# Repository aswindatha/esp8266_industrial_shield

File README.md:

# esp8266_industrial_shield

Industrial 8-channel motor controller (ESP32-WROOM-32E), 100 × 100 mm.

## Repository structure

| Path | What it is |
|---|---|
| **`2layer_production/`** | **FINAL, fabrication-ready board.** 0 DRC, 0 ERC, complete fab package and quotation. Use this. |
| **`1layer_prototype/`** | Single-layer conversion experiment. **Not fabrication-ready** (18 unconnected). Study only. |
| `tools/` | Routing, auditing and BOM scripts used to verify the boards. |
| `robu-search/` | Portable Robu.in part-search skill kit (installed into OpenCode). |

The root-level `ind_8ch_motor_ctrl.*` files are the working copy of the
2-layer production board (identical to `2layer_production/`).

## 2-layer production board — status

- **PCB DRC:** 0 violations, 0 unconnected (all severities)
- **ERC:** 0 violations
- **Production audit:** 23/23 checks PASS (`python3 tools/production_audit.py`)
- **Layers:** 2 Cu, 716 track segments, 83 vias, 50 components all on F.Cu
- **Min features:** 0.2624 mm track, 0.2516 mm clearance, 0.20 mm drill, 0.30 mm copper-to-edge
- **Fab package:** `2layer_production/ind_8ch_motor_ctrl_FAB_PACKAGE.zip` (24 files)

See `2layer_production/README.md` and `FINAL_VERIFICATION.md` for full evidence.

## Prototype quotation (5 boards, 2026-11-23)

| Item | ₹ |
|---|---:|
| PCB (cuCircuits, FR4 TG135, 1.6 mm, HASL-RoHs, tested) | 1,692.75 |
| Components (Robu.in, verified) | 3,860.55 |
| **Subtotal (excl. terminal blocks & shipping)** | **5,553.30** |

Source: `COST_REPORT.md`.

## Important limitations

- **Single-layer:** not achievable as a DRC-clean board with the current netlist
  and KiCad's copper-only connectivity model. Full analysis in
  `SINGLE_LAYER_FINAL.md` and `1layer_prototype/README.md`.
- **India compliance:** WPC ETA required for the ESP32 2.4 GHz radio; RoHS CoCs
  needed. See `INDIA_MANUFACTURING_REPORT.md`.
- **Firmware:** ESP32 IO0/EN are not broken out — pre-flash firmware.
- **Next revision:** add an input fuse, flyback diodes and extra decoupling
  capacitors via a proper re-layout (they could not be inserted into the
  finished copper without breaking DRC).

## Reproduce verification

```bash
kicad-cli pcb drc --exit-code-violations 2layer_production/ind_8ch_motor_ctrl.kicad_pcb
kicad-cli sch erc --exit-code-violations 2layer_production/ind_8ch_motor_ctrl.kicad_sch
python3 tools/production_audit.py
```

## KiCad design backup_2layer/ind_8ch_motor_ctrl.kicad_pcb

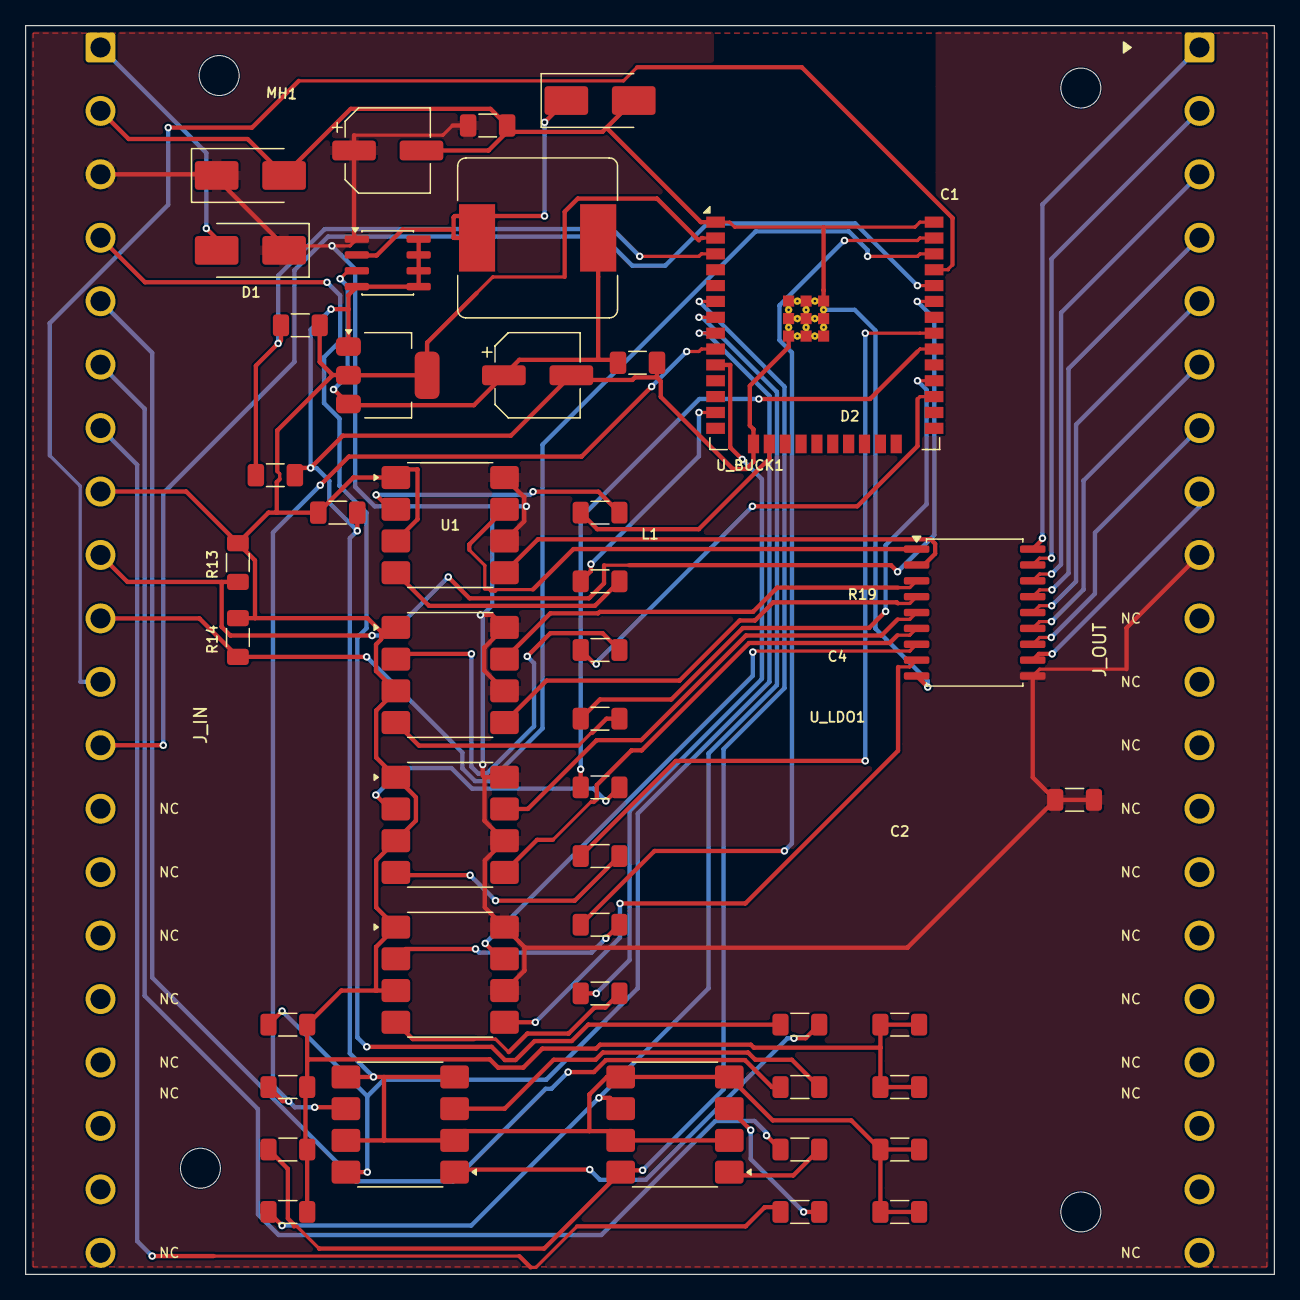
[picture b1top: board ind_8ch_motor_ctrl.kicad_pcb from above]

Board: 2 copper layers, 100.0 x 100.0 mm, 50 parts (0 on the bottom side), 55 nets.

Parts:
C1, C2, C3, C4: 10uF; C_1206_3216Metric_Pad1.33x1.80mm_HandSolder
C_BULK1, C_BULK2: 220uF/25V; CP_Elec_6.3x7.7
D1, D2: SS34; D_SMB_Handsoldering
D_TVS1: SMBJ15A-13-F; D_SMB_Handsoldering
J_IN: INPUT; TerminalBlock_CUI_TB007-508-20_1x20_P5.08mm_Horizontal
J_OUT: OUTPUT; TerminalBlock_CUI_TB007-508-20_1x20_P5.08mm_Horizontal
L1: 33uH; L_Bourns_SRR1260
MH1, MH2, MH3, MH4: MountingHole_3.2mm
R1, R2, R3, R4, R5, R6, R7, R8: 330R; R_1206_3216Metric_Pad1.30x1.75mm_HandSolder
R9, R10, R11, R12: 2.2k; R_1206_3216Metric_Pad1.30x1.75mm_HandSolder
R13, R14, R15, R16, R17, R18: 4.7k; R_1206_3216Metric_Pad1.30x1.75mm_HandSolder
R19: 10k; R_1206_3216Metric_Pad1.30x1.75mm_HandSolder
R_J1, R_J2, R_J3, R_J4, R_J5: 0R; R_1206_3216Metric_Pad1.30x1.75mm_HandSolder
U1, U2, U3, U4, U5, U6: LTV-827S; SOP-8_6.605x9.655mm_P2.54mm
U_BUCK1: XL1509-5.0; SOIC-8_3.9x4.9mm_P1.27mm
U_DRV1: ULN2803; SOIC-18W_7.5x11.6mm_P1.27mm
U_LDO1: AMS1117-3.3; SOT-223-3_TabPin2
U_MCU1: ESP32-WROOM-32E

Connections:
/3V3_RAIL: C3.1, J_IN.8, R13.2, R14.2, R15.2, R16.2, R17.2, R18.2, R19.2, R_J1.1, R_J1.2, R_J2.1, R_J2.2, U1.1, U1.3, U2.1, U2.3, U3.1, U3.3, U4.1, U4.3, U_LDO1.2 (VO), U_MCU1.2 (VDD)
/5V_RAIL: C2.1, C_BULK2.1, L1.2, U_BUCK1.3 (FB), U_LDO1.3 (VI)
/12V_PROT: C1.1, C_BULK1.1, D1.1 (K), D_TVS1.1 (K), J_IN.3, J_OUT.9, R_J4.1, R_J4.2, U1.6, U1.8, U2.6, U2.8, U3.6, U3.8, U4.6, U4.8, U_BUCK1.1 (VIN), U_DRV1.10 (COM)
/12V_RAW: D1.2 (A), J_IN.1
/GND: C1.2, C2.2, C3.2, C4.2, C_BULK1.2, C_BULK2.2, D2.2 (A), D_TVS1.2 (A), J_IN.2, R_J3.1, R_J3.2, R_J5.1, R_J5.2, U5.2, U5.4, U5.5, U5.7, U6.2, U6.4, U6.5, U6.7, U_BUCK1.4 (~EN), U_BUCK1.5 (GND), U_BUCK1.6 (GND), U_BUCK1.7 (GND), U_BUCK1.8 (GND), U_DRV1.9 (GND), U_LDO1.1 (GND), U_MCU1.1 (GND), U_MCU1.15 (GND), U_MCU1.38 (GND), U_MCU1.39 (GND)
/I2C_SCL: J_IN.10, R14.1, U_MCU1.36 (IO22)
/I2C_SDA: J_IN.9, R13.1, U_MCU1.33 (IO21)
/M1_DRV: U1.7, U_DRV1.1 (I1)
/M1_GPIO: R2.1, U_MCU1.13 (IO14)
/M1_LED: R1.2, U1.2
/M2_DRV: U1.5, U_DRV1.2 (I2)
/M2_GPIO: R3.1, U_MCU1.27 (IO16)
/M2_LED: R2.2, U1.4
/M3_DRV: U2.7, U_DRV1.3 (I3)
/M3_GPIO: R4.1, U_MCU1.28 (IO17)
/M3_LED: R3.2, U2.2
/M4_DRV: U2.5, U_DRV1.4 (I4)
/M4_GPIO: R1.1, U_MCU1.16 (IO13)
/M4_LED: R4.2, U2.4
/M5_DRV: U3.7, U_DRV1.5 (I5)
/M5_GPIO: R8.1, U_MCU1.10 (IO25)
/M5_LED: R5.2, U3.2
/M6_DRV: U3.5, U_DRV1.6 (I6)
/M6_GPIO: R5.1, U_MCU1.30 (IO18)
/M6_LED: R6.2, U3.4
/M7_DRV: U4.7, U_DRV1.7 (I7)
/M7_GPIO: R6.1, U_MCU1.31 (IO19)
/M7_LED: R7.2, U4.2
/M8_DRV: U4.5, U_DRV1.8 (I8)
/M8_GPIO: R7.1, U_MCU1.37 (IO23)
/M8_LED: R8.2, U4.4
/MCU_EN: C4.1, R19.1, U_MCU1.3 (EN)
/MOT1: J_OUT.1, U_DRV1.18 (O1)
/MOT2: J_OUT.2, U_DRV1.17 (O2)
/MOT3: J_OUT.3, U_DRV1.16 (O3)
/MOT4: J_OUT.4, U_DRV1.15 (O4)
/MOT5: J_OUT.5, U_DRV1.14 (O5)
/MOT6: J_OUT.6, U_DRV1.13 (O6)
/MOT7: J_OUT.7, U_DRV1.12 (O7)
/MOT8: J_OUT.8, U_DRV1.11 (O8)
/SENS1_A: R9.2, U5.1
/SENS1_COL: R15.1, U5.8, U_MCU1.8 (IO32)
/SENS2_A: R10.2, U5.3
/SENS2_COL: R16.1, U5.6, U_MCU1.9 (IO33)
/SENS3_A: R11.2, U6.1
/SENS3_COL: R17.1, U6.8, U_MCU1.6 (IO34)
/SENS4_A: R12.2, U6.3
/SENS4_COL: R18.1, U6.6, U_MCU1.7 (IO35)
/SENS_IN1: J_IN.4, R9.1
/SENS_IN2: J_IN.5, R10.1
/SENS_IN3: J_IN.6, R11.1
/SENS_IN4: J_IN.7, R12.1
/SW_BUCK: D2.1 (K), L1.1, U_BUCK1.2 (OUT)
/UART_RX: J_IN.12, U_MCU1.34 (RXD0/IO3)
/UART_TX: J_IN.11, U_MCU1.35 (TXD0/IO1)

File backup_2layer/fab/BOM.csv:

Reference,Value,Footprint,Pads,Side
R_J1,0R,Resistor_SMD:R_1206_3216Metric_Pad1.30x1.75mm_HandSolder,2,F.Cu
R_J2,0R,Resistor_SMD:R_1206_3216Metric_Pad1.30x1.75mm_HandSolder,2,F.Cu
R_J3,0R,Resistor_SMD:R_1206_3216Metric_Pad1.30x1.75mm_HandSolder,2,F.Cu
R_J4,0R,Resistor_SMD:R_1206_3216Metric_Pad1.30x1.75mm_HandSolder,2,F.Cu
R_J5,0R,Resistor_SMD:R_1206_3216Metric_Pad1.30x1.75mm_HandSolder,2,F.Cu
R19,10k,Resistor_SMD:R_1206_3216Metric_Pad1.30x1.75mm_HandSolder,2,F.Cu
C1,10uF,Capacitor_SMD:C_1206_3216Metric_Pad1.33x1.80mm_HandSolder,2,F.Cu
C2,10uF,Capacitor_SMD:C_1206_3216Metric_Pad1.33x1.80mm_HandSolder,2,F.Cu
C3,10uF,Capacitor_SMD:C_1206_3216Metric_Pad1.33x1.80mm_HandSolder,2,F.Cu
C4,10uF,Capacitor_SMD:C_1206_3216Metric_Pad1.33x1.80mm_HandSolder,2,F.Cu
R10,2.2k,Resistor_SMD:R_1206_3216Metric_Pad1.30x1.75mm_HandSolder,2,F.Cu
R11,2.2k,Resistor_SMD:R_1206_3216Metric_Pad1.30x1.75mm_HandSolder,2,F.Cu
R12,2.2k,Resistor_SMD:R_1206_3216Metric_Pad1.30x1.75mm_HandSolder,2,F.Cu
R9,2.2k,Resistor_SMD:R_1206_3216Metric_Pad1.30x1.75mm_HandSolder,2,F.Cu
C_BULK1,220uF/25V,Capacitor_SMD:CP_Elec_6.3x7.7,2,F.Cu
C_BULK2,220uF/25V,Capacitor_SMD:CP_Elec_6.3x7.7,2,F.Cu
R1,330R,Resistor_SMD:R_1206_3216Metric_Pad1.30x1.75mm_HandSolder,2,F.Cu
R2,330R,Resistor_SMD:R_1206_3216Metric_Pad1.30x1.75mm_HandSolder,2,F.Cu
R3,330R,Resistor_SMD:R_1206_3216Metric_Pad1.30x1.75mm_HandSolder,2,F.Cu
R4,330R,Resistor_SMD:R_1206_3216Metric_Pad1.30x1.75mm_HandSolder,2,F.Cu
R5,330R,Resistor_SMD:R_1206_3216Metric_Pad1.30x1.75mm_HandSolder,2,F.Cu
R6,330R,Resistor_SMD:R_1206_3216Metric_Pad1.30x1.75mm_HandSolder,2,F.Cu
R7,330R,Resistor_SMD:R_1206_3216Metric_Pad1.30x1.75mm_HandSolder,2,F.Cu
R8,330R,Resistor_SMD:R_1206_3216Metric_Pad1.30x1.75mm_HandSolder,2,F.Cu
L1,33uH,Inductor_SMD:L_Bourns_SRR1260,2,F.Cu
R13,4.7k,Resistor_SMD:R_1206_3216Metric_Pad1.30x1.75mm_HandSolder,2,F.Cu
R14,4.7k,Resistor_SMD:R_1206_3216Metric_Pad1.30x1.75mm_HandSolder,2,F.Cu
R15,4.7k,Resistor_SMD:R_1206_3216Metric_Pad1.30x1.75mm_HandSolder,2,F.Cu
R16,4.7k,Resistor_SMD:R_1206_3216Metric_Pad1.30x1.75mm_HandSolder,2,F.Cu
R17,4.7k,Resistor_SMD:R_1206_3216Metric_Pad1.30x1.75mm_HandSolder,2,F.Cu
R18,4.7k,Resistor_SMD:R_1206_3216Metric_Pad1.30x1.75mm_HandSolder,2,F.Cu
U_LDO1,AMS1117-3.3,Package_TO_SOT_SMD:SOT-223-3_TabPin2,4,F.Cu
U_MCU1,ESP32-WROOM-32E,RF_Module:ESP32-WROOM-32E,59,F.Cu
J_IN,INPUT,TerminalBlock_CUI_TB007-508-20_1x20_P5.08mm_Horizontal,20,F.Cu
U1,LTV-827S,Package_SO:SOP-8_6.605x9.655mm_P2.54mm,8,F.Cu
U2,LTV-827S,Package_SO:SOP-8_6.605x9.655mm_P2.54mm,8,F.Cu
U3,LTV-827S,Package_SO:SOP-8_6.605x9.655mm_P2.54mm,8,F.Cu
U4,LTV-827S,Package_SO:SOP-8_6.605x9.655mm_P2.54mm,8,F.Cu
U5,LTV-827S,Package_SO:SOP-8_6.605x9.655mm_P2.54mm,8,F.Cu
U6,LTV-827S,Package_SO:SOP-8_6.605x9.655mm_P2.54mm,8,F.Cu
J_OUT,OUTPUT,TerminalBlock_CUI_TB007-508-20_1x20_P5.08mm_Horizontal,20,F.Cu
D_TVS1,SMBJ15A-13-F,Diode_SMD:D_SMB_Handsoldering,2,F.Cu
D1,SS34,Diode_SMD:D_SMB_Handsoldering,2,F.Cu
D2,SS34,Diode_SMD:D_SMB_Handsoldering,2,F.Cu
U_DRV1,ULN2803,Package_SO:SOIC-18W_7.5x11.6mm_P1.27mm,18,F.Cu
U_BUCK1,XL1509-5.0,Package_SO:SOIC-8_3.9x4.9mm_P1.27mm,8,F.Cu

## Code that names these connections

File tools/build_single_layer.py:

"""
Build the SINGLE-LAYER variant (working copy). The 2-layer design is preserved in
ind_8ch_motor_ctrl_2LAYER_backup.zip and backup_2layer/.

Changes vs 2-layer version:
  - B.Cu copper removed entirely (no tracks, no vias, no zones)
  - 5.08 mm CUI terminal blocks replaced with 5.00 mm Altech AK100 20-position
    blocks (101.05 mm body instead of 103.25 mm -> ~0.5 mm overhang per end)
  - terminal blocks repositioned to y=2.5 for symmetric end overhang
"""
import pcbnew, os
ROOT=os.path.dirname(os.path.dirname(os.path.abspath(__file__)))
PCB=os.path.join(ROOT,"ind_8ch_motor_ctrl.kicad_pcb")
LIB=r"C:\Users\aswin\AppData\Local\Programs\KiCad\10.0\share\kicad\footprints"
TBLIB="TerminalBlock_Altech.pretty"
TBNAME="Altech_AK100_1x20_P5.00mm"
MM=pcbnew.FromMM
V=lambda x,y: pcbnew.VECTOR2I(MM(x),MM(y))

IN_PINS={1:"12V_RAW",2:"GND",3:"12V_PROT",4:"SENS_IN1",5:"SENS_IN2",6:"SENS_IN3",7:"SENS_IN4",
         8:"3V3_RAIL",9:"I2C_SDA",10:"I2C_SCL",11:"UART_TX",12:"UART_RX"}
OUT_PINS={1:"MOT1",2:"MOT2",3:"MOT3",4:"MOT4",5:"MOT5",6:"MOT6",7:"MOT7",8:"MOT8",9:"12V_PROT"}
USED=set(IN_PINS.values())|set(OUT_PINS.values())
TB_POS={"J_IN":(6.0,2.5),"J_OUT":(94.0,2.5)}

b=pcbnew.LoadBoard(PCB)
print("loaded footprints:",len(list(b.GetFootprints())))

# 1) wipe all routing and zones (both layers)
for t in list(b.GetTracks()): b.RemoveNative(t)
for z in list(b.Zones()): b.RemoveNative(z)
print("cleared tracks/zones")

# 2) remove old TBs and add 5.00 mm ones
for ref in ("J_IN","J_OUT"):
    fp=b.FindFootprintByReference(ref)
    if fp: b.RemoveNative(fp)
nets={n:b.FindNet("/"+n) for n in USED}
for ref,pinmap in (("J_IN",IN_PINS),("J_OUT",OUT_PINS)):
    fp=pcbnew.FootprintLoad(os.path.join(LIB,TBLIB),TBNAME)
    fp.SetReference(ref); fp.SetValue("INPUT" if ref=="J_IN" else "OUTPUT")
    fp.SetPosition(V(*TB_POS[ref])); fp.SetOrientationDegrees(-90)
    b.Add(fp)
    for p in fp.Pads():
        n=int(p.GetNumber()); nm=pinmap.get(n)
        if nm: p.SetNet(nets[nm])
        else: p.SetNetCode(0)
    cb=fp.GetBoundingBox(False,False)
    print(ref,"bbox x[%.2f,%.2f] y[%.2f,%.2f]"%(pcbnew.ToMM(cb.GetLeft()),pcbnew.ToMM(cb.GetRight()),pcbnew.ToMM(cb.GetTop()),pcbnew.ToMM(cb.GetBottom())))

# 3) remove any NC silkscreen text from the old board and re-add at correct positions
for d in list(b.GetDrawings()):
    if isinstance(d,pcbnew.PCB_TEXT) and d.GetText()=="NC": b.RemoveNative(d)
for ref,pinmap in (("J_IN",IN_PINS),("J_OUT",OUT_PINS)):
    fp=b.FindFootprintByReference(ref)
    for p in fp.Pads():
        if int(p.GetNumber()) in pinmap: continue
        q=p.GetPosition(); inward=MM(3.2) if ref=="J_IN" else MM(-3.2)
        t=pcbnew.PCB_TEXT(b); t.SetText("NC")
        t.SetPosition(pcbnew.VECTOR2I(q.x+inward,q.y))
        t.SetLayer(pcbnew.F_SilkS)
        t.SetTextSize(pcbnew.VECTOR2I(MM(0.8),MM(0.8))); t.SetTextThickness(MM(0.12))
        b.Add(t)

# 4) ensure no B.Cu copper exists; F.Cu only
for t in list(b.GetTracks()):
    if t.GetLayer()==pcbnew.B_Cu: b.RemoveNative(t)

pcbnew.SaveBoard(PCB,b)
b2=pcbnew.LoadBoard(PCB)
print("tracks:",len(list(b2.GetTracks())),"vias:",len([t for t in b2.GetTracks() if isinstance(t,pcbnew.PCB_VIA)]),"zones:",len(list(b2.Zones())))
print("saved single-layer base:",PCB)
